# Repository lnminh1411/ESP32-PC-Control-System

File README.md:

# ESP32 PC Control System

### Why would I put myself through the suffering

I needed my PC online at all time, because sometime at school or work I need to remote
control the PC back at home. And as I measured, the idle time alone costs me ~40KWh (~7usd) per month.
So, I built this for 30usd instead of buying a boring and expensive IP KVM, while adding a tons more
features to fit my over-engineering stuffs hobby.

<table><tr><td width="190" valign="top">

</td><td valign="top">

An ESP32-S3 carrier board that lives inside a PC case. It drives three 2.4"
displays, turns the PC on and off, presses the motherboard's reset line and
works a 4-button door remote, all from one ESP32-S3-N16R8 module on a custom
2-layer PCB. A Windows helper feeds it the PC's stats and carries its
commands back to the PC.

</td></tr></table>

## Companion projects

This is the main project; the others work with it.

| Project | Role for this board |
|---|---|
| [PC Hardware Control Service](https://github.com/lnminh1411/PC-Hardware-Control-Service) (PcHwCtl) | Windows service the helper calls over the `PcHwCtl` pipe: sensor feed, fans and RGB, monitors, power actions, Process Lasso night config, webcam presence and screenshots |
| [Local LLM stack](https://github.com/lnminh1411/local-llm-stack) | Local AI stack. Its status shows on the panels, and the Discord Local Agent tab controls it through the helper's `!ai` relay |
| [ESP32 Human Presence Radar](https://github.com/lnminh1411/ESP32-Human-Presence-Radar) | Add-on presence board (mmWave radar and ToF) for the presence rules (AFK, away, intruder lock, night). New; the link to this board is in development |

*Every face, captured from the board with `shot`. The stats are made up; the
layout is real. What each panel shows and when: [docs/screens.md](docs/screens.md).*

## What it does

- **Three status panels:** PC stats, media with cover art, Claude and
  Antigravity quota and the local AI while the PC is on; a GIF, the weather
  and a clock while it is off.
- **Power control:** Wake-on-LAN and USB wake, sleep / hibernate / restart /
  shutdown / lock through PcHwCtl on the PC, and a hardware reset for a hung PC.
- **Discord bot:** a control panel for the door, the PC, its RGB, fans,
  monitors and local AI agent, and the board itself; PC, weather and log
  channels, copied to Pushover.
- **Weather:** rain nowcast and warnings (Drizzle to Typhoon) that follow
  your phone through OwnTracks, OpenWeather minute rain and GDACS typhoons.
- **Night mode:** dims everything, parks background processes on E-cores,
  sleeps the PC after an idle hour at night and hibernates it when you leave
  home.
- **Door remote:** four opto-isolated keyfob buttons.

## Parts

- **Board:** rev 3.1 carrier, 45.7 x 138.2 mm, 3 ST7789 panels on one SPI
  bus, 5 optocouplers, a 12 V boost ([docs/hardware.md](docs/hardware.md)).
- **Firmware:** ESP-IDF 5.5.6 with LovyanGFX, in [`firmware/`](firmware/)
  ([docs/firmware.md](docs/firmware.md)).
- **PC helper:** `ESP32-Helper.exe`, a .NET 10 Windows service with a
  user-session half, in [`host/pc_stats/`](host/pc_stats/)
  ([docs/helper.md](docs/helper.md)).
- **PcHwCtl:** a separate repo on the PC that owns sensors, power actions,
  RGB, fans, monitors, Process Lasso rules, the desk camera check and
  screenshots; the helper talks to it over its named pipe.
- **LocalAIHost:** a separate repo on the PC that hosts the local language
  model; the helper relays the board's local AI commands to it and polls its
  status hub.
- **Case:** a 3D-printed block, lid and display mask in
  [`enclosure/`](enclosure/).

## Quick start

1. Copy `firmware/main/settings_example.h` to `settings.h` and fill in the
   secrets ([docs/settings.md](docs/settings.md)).
2. Build and flash over USB ([docs/build-and-flash.md](docs/build-and-flash.md)):

   ```bash
   firmware/idf.cmd build
   python scripts/idf_flash.py --no-build
   ```

3. Build and install the PC helper from an elevated shell
   ([docs/helper.md](docs/helper.md#build-and-install)):

   ```bash
   host/pc_stats/build.cmd
   powershell -ExecutionPolicy Bypass -File host/pc_stats/install.ps1
   ```

4. Set the BIOS and Windows up for Wake-on-LAN
   ([docs/power-and-night.md](docs/power-and-night.md)), then set a home with
   `weather home <lat>,<lon>` on the console ([docs/console.md](docs/console.md)).

## Documentation

| Page | Covers |
|---|---|
| [screens.md](docs/screens.md) | The faces, warnings on them, PC usage warnings |
| [hardware.md](docs/hardware.md) | The board, pin map, assembly, the eFuse fix, bring-up findings, building the PCB |
| [firmware.md](docs/firmware.md) | Modules, display pipeline, tasks, ESP-IDF options, PSRAM hardening |
| [console.md](docs/console.md) | Every console command |
| [power-and-night.md](docs/power-and-night.md) | Power control, Wake-on-LAN setup, night and low power mode, the power-on brownout |
| [discord.md](docs/discord.md) | Channels, the control panel, Pushover, screenshots |
| [weather.md](docs/weather.md) | Weather sources, nowcast, warnings, OwnTracks, Pushover, call budgets |
| [helper.md](docs/helper.md) | The PC helper; full reference in [host/pc_stats/README.md](host/pc_stats/README.md) |
| [settings.md](docs/settings.md) | `settings.h`, the secrets, and [every other key](docs/settings-reference.md) |
| [build-and-flash.md](docs/build-and-flash.md) | Building, flashing, uploads, screenshots, CI |
| [layouts.md](docs/layouts.md) | JSON dashboard layouts |
| [benchmark.md](docs/benchmark.md) | Memory and speed measurements |
| [security.md](docs/security.md) | Accepted risks, where secrets live, what to check if an attack is suspected |
| [pc-power-detection.md](docs/pc-power-detection.md), [recovery-and-physical-access.md](docs/recovery-and-physical-access.md) | Design notes |
| [documentations_summary.md](docs/documentations_summary.md) | Every doc in the repo in one list |

## Repository layout

| Path | Contents |
|---|---|
| [`firmware/`](firmware/) | The board's firmware |
| [`host/pc_stats/`](host/pc_stats/) | The PC helper ([README](host/pc_stats/README.md)) |
| [`pcb/`](pcb/) | atopile netlist, KiCad board, footprints ([README](pcb/README.md)) |
| [`scripts/`](scripts/) | PCB build chain, flashing, uploads, screenshots ([README](scripts/README.md)) |
| [`enclosure/`](enclosure/) | CadQuery model of the case ([README](enclosure/README.md)) |
| [`docs/`](docs/) | The pages above |

## Status

Rev 3.1 is fabricated and assembled, and the firmware runs on it: all three
panels, PC power detection, the stats link, Wi-Fi, Wake PC, the Discord bot,
live weather with OwnTracks and Pushover, and night mode are in daily use.
Still to do: test the door buttons B1-B4 on the real keyfob, and
build the firmware in CI.

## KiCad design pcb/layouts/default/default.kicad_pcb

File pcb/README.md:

# Carrier PCB (atopile + KiCad), rev 3.1

Single-file atopile project: [`main.ato`](main.ato), the source of truth
for the netlist. It has no external imports: every part is defined locally
with explicit pins and footprint. The KiCad board is
`layouts/default/default.kicad_pcb`, generated and routed by the scripts in
[`../scripts/`](../scripts/README.md).

## Build

```bash
cd pcb
PYTHONIOENCODING=utf-8 ato build
```

`PYTHONIOENCODING=utf-8` works around a Windows-console crash in atopile's
`designator-map` step (a `rich`/`colorama` Unicode bug). `ato build` only
writes the netlist; [`../scripts/sync_netlist_to_board.py`](../scripts/sync_netlist_to_board.py)
puts it onto the board. The full chain is in
[`../scripts/README.md`](../scripts/README.md).

If you regenerate `ato.yaml`, the version key is **`ato-version`**
(hyphenated). The underscore form fails with an unrelated-looking
"not valid SemVer string" error.

## Board

- **L-shaped, 45.7 x 138.2 mm**, 1.6 mm thick, **2 layers**, DRC 0/0.
  Main body 45.7 x 88.0 mm, plus a 16.7 mm strip down the east edge that
  carries displays 2 and 3.
- The ESP32 module is mounted **rotated 180°**: the USB-C end overhangs the
  **top** edge (the enclosure's plug-in side), the PCB antenna is at the
  bottom of the module with a no-copper keepout under it (all layers,
  Y = 54.5-67.5 mm). The main body continues below the antenna to hold the
  RST pair, keyfob socket and status LED, so expect slightly less WiFi/BLE
  range than with the antenna over air.
- The boost, the 5 optos and 11 of the axial resistors sit **under the
  module**, which rides ~11 mm up on its sockets (boost top ~6.5 mm, ~4.5 mm
  clearance).
- **Displays plug in directly**: GMT024-08-SPI8P 2.4" panels (PCB 46.9 x
  71 mm, 8-pin header) in right-angle sockets at **51.9 mm pitch**,
  overhanging the east edge 1 mm so the panel header clears. Pin order
  GND VCC SCL SDA RST DC CS BL = socket pads 1-8. **Panels hang down below
  the board**, screen facing out, header edge up: the only way round that
  puts panel pin 1 (GND) on pad 1. Plugged in standing up, all 8 pins
  reverse (5V onto CS).
- Mounting holes (M2.5): top-right, bottom-left of the main body, between
  displays 1/2 and between displays 2/3.

### Stackup and routing

- **F.Cu carries all routing; B.Cu is one unbroken GND pour** except 5
  short B.Cu jumpers (27 mm total, 6 vias) where a line must cross the
  display bus or the opto anode bus. No B.Cu jumper crosses under SCK or
  MOSI. Every part is through-hole, so the pour connects every GND pad.
- **5V is a routed 0.4-0.5 mm track** (net class `Power`: 0.5 mm track,
  0.8/0.4 mm via, covers 5V and 12V) from J1 pin 21 down the west side of
  J1 to a trunk under the display sockets. 12V (boost -> opto collectors,
  keyfob) is a 0.5 mm bus, 0.4 mm to the keyfob. Nothing uses 3V3.
- **Display bus**: SCK, MOSI and DC are a true daisy chain on F.Cu (MCU ->
  display 1 -> 2 -> 3, every segment pad to pad, no T-junctions, no vias).
  SCK and MOSI each pass a **33R THT series resistor** (source termination;
  fit a wire link to bypass) lying flat in the top-right corner. CS1-3 and
  RST1-3 are point-to-point. Chain lengths: SCK 144 mm, MOSI 146 mm, DC
  147 mm. Verified by [`../scripts/check_spi_topology.py`](../scripts/check_spi_topology.py).
- **Everything is hand-routed** by [`../scripts/route_spi.py`](../scripts/route_spi.py);
  Freerouting stays only as a safety net. Every track corner is a 45°
  chamfer.
- **SI note**: on 2 layers the SPI return path is the B.Cu pour 1.6 mm
  below, and three jumper slots (BL2, BL3, RST2, each <= 6 mm) cross under
  the bus lanes in the strip. The bus runs at 40 MHz (see the root README);
  if a panel ever shows noise, lower the SPI clock first.

**Net names** are declared explicitly in `main.ato` (`gnd`, `v5`, `v12`,
`disp_*`, `mb_rst`, `mb_rst_gnd`, `led_a`). Without them atopile names each
net after a random member pin.

**Board references come from the atopile instance names** (J1 `mcu.left`,
J2 `mcu.right`, J3-J5 displays, J6 RST pair, J7 keyfob, PS1 boost, U1-U5
`opto1-5`, R1-R13, D1 LED), not atopile's declaration-order numbers, so
adding or removing a part does not renumber the rest.

### Silkscreen

- Every off-board connector has per-pin labels (displays
  GND/5V/SCL/SDA/RSTn/DC/CSn/BLn, keyfob 12V/B1-B4/GND, RST pair).
- **Module**: "USB-C END (TOP EDGE)" at the top edge, "ANTENNA END" at the
  bottom; pin 1 of each row labelled (left row J2 = GND, right row J1 = 3V3).
- **Resistors**: the value is printed inside each body (`270R` x6, `10k`
  x5, `33R` x2).
- **PC817 optos**: pin 1 (LED anode) is the square pad and has a **dot**,
  matching the part's moulded dot. Place dot to dot.

## Parts

| Connector / part | Pins | Footprint / notes |
|---|---|---|
| N16R8 module socket (J1, J2) | 44 (2x22) | Female; the module plugs in on its own male headers. Socket row spacing is 25.4 mm, measured off the real module (not Espressif's 22.86 mm reference). |
| Boost converter (PS1) | 4 | CKCS BS01 5V->12V, custom footprint `footprints/ESP32PCC.pretty/Boost_CKCS_BS01` (pads measured ±0.15 mm). Mount on 4 single male pins: long end down through the board, short end up through the module. Set the A+B bridges for 12V and meter it before connecting the keyfob. |
| Keyfob connector (J7) | 1x6 | Female right-angle, bottom edge of the main body: 1 = 12V, 2-5 = B1-B4 (opto 1-4 emitters), 6 = GND |
| Display sockets (J3-J5) | 3x 1x8 | Female right-angle, see Board above |
| PC817 bank (U1-U5) | 5x DIP-4 | `Package_DIP:DIP-4_W7.62mm`, turned 180°, outputs facing the west edge |
| Status LED (D1) | 5 mm THT | Pad 1 (square) = cathode; below the module beside J6, for a light pipe |
| Resistors (R1-R13) | 6x 270R + 5x 10k + 2x 33R | Axial DIN0207 lying flat, leads bent to the measured 8.128 mm pitch: 5 opto LED drive, 1 status LED, 5 opto-GPIO pull-downs, 2 SCK/MOSI series terminations |
| Motherboard RST pair (J6) | 1x2 | Female right-angle, west edge below the module: 1 = opto 5 collector (to RST+), 2 = emitter (to RST GND) |

The PC link (USB-OTG, the module's second USB-C port) is a Type-E-to-Type-C
cable straight to the motherboard's internal USB header. No carrier copper.

## Pin mapping

The table is in the [root README](../README.md#pin-map-rev-31). Design
reasons behind it:

- Display bus on FSPI IO_MUX pins (MOSI 11, SCK 12). Per-display RST lines
  so a hung panel can be reset alone. BL1 is GPIO3 (pin 13, below the bus):
  pin 19 sits inside the loop the SCK/MOSI risers make, and a jumper there
  would cut the GND pour under both fast lines. GPIO3 is a strap pin only
  when the JTAG-select eFuse is burnt (it isn't by default).
- Opto drive GPIOs (B1-B4 = 39/40/41/42, reset = 1) follow J2's pin order so
  the drive lines reach the optos without crossing. GPIO1 for the reset
  line has no boot-time pull-up glitch.
- **Every opto GPIO has a 10k pull-down.** GPIO39-42 are JTAG pins that can
  come up with a ~45k pull-up during reset/boot/flashing, and ~50 µA through
  an opto is enough for the fob's CMOS button input to see a phantom press.
  With 10k the pin sits at ~0.6 V, below the LED's ~1.1 V turn-on.
- Display VCC is the module's 5Vin, not 3V3, on purpose: the panels have
  their own 3.3V regulator. **Bridge the module's `IN-OUT` jumper**: by
  default `5VIN` is input-only and the carrier gets no 5V.
- Unused module GPIOs: 0, 4, 7, 13, 14, 21, 38, 45, 46, 47, 48 (48 = onboard
  WS2812).

### Opto GPIO rules (firmware)

All five opto pins are initialised the same way, implemented in
[`../firmware/main/optos.cpp`](../firmware/main/optos.cpp):
pre-stage the output latch LOW with `gpio_set_level(pin, 0)` while the pin
is still Hi-Z, then switch it to an output with `gpio_config`. The pin goes
Hi-Z (held low by the 10k) -> driven LOW, with no window where it can drive
HIGH. `optosInit()` is the first thing `app_main` runs. Pulses are ended by
one-shot `esp_timer`s.

- Reset is a short pulse only (HIGH 200 ms, then LOW). Holding it HIGH keeps
  the PC in reset; it never powers it off.
- Never pulse reset at boot: the ESP is powered from the PC's USB, so a
  reset at boot could loop forever.
- Never use `INPUT_PULLUP` on an opto GPIO: the ~45k internal pull-up
  against the 10k pull-down lands near the opto LED's turn-on voltage.
- The board has no hardware interlock between door buttons; the
  one-at-a-time rule and the 500 ms gap live in firmware.

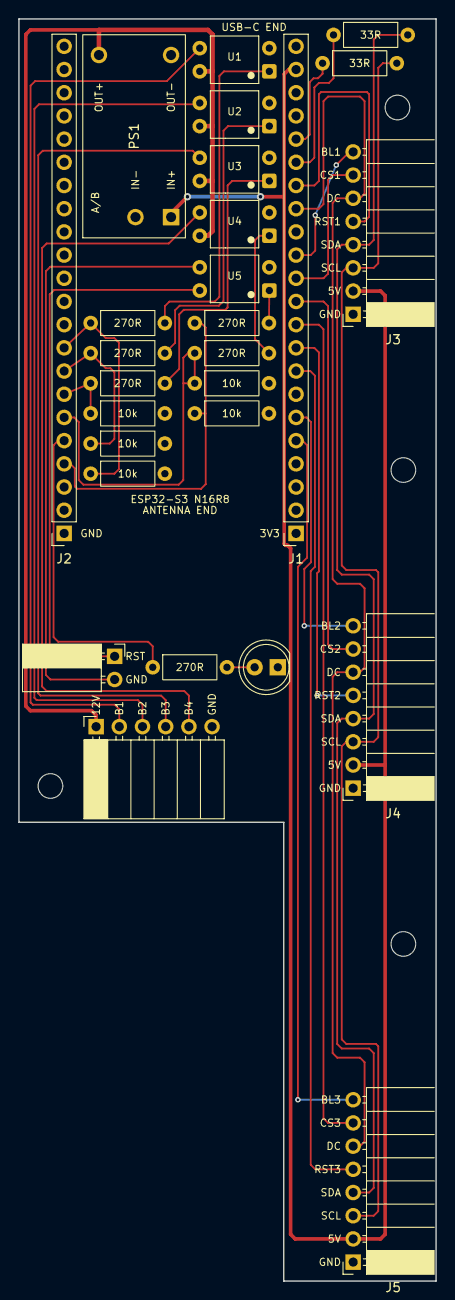
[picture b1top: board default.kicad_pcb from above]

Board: 2 copper layers, 45.7 x 138.2 mm, 31 parts (0 on the bottom side), 35 nets.

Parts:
D1: main.ato:StatusLED; LED_D5.0mm
J1, J2: main.ato:Header1x22; PinSocket_1x22_P2.54mm_Vertical
J3, J4, J5: main.ato:DisplaySocket; PinSocket_1x08_P2.54mm_Horizontal
J6: main.ato:IsolatedPair; PinSocket_1x02_P2.54mm_Horizontal
J7: main.ato:KeyfobSocket; PinSocket_1x06_P2.54mm_Horizontal
MH1, MH2, MH3, MH4: MountingHole_2.7mm_M2.5
PS1: main.ato:BoostModuleBS01; Boost_CKCS_BS01
R1, R2, R3, R4, R5, R6: 270R; R_Axial_DIN0207_L6.3mm_D2.5mm_P10.16mm_Horizontal
R7, R10, R11, R12, R13: 10k; R_Axial_DIN0207_L6.3mm_D2.5mm_P10.16mm_Horizontal
R8, R9: 33R; R_Axial_DIN0207_L6.3mm_D2.5mm_P10.16mm_Horizontal
U1, U2, U3, U4, U5: main.ato:Optocoupler; DIP-4_W7.62mm

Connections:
btn1: J7.2, U1.3
btn2: J7.3, U2.3
btn3: J7.4, U3.3
btn4: J7.5, U4.3
disp_bl1: J1.13, J3.8
disp_bl2: J1.6, J4.8
disp_bl3: J1.5, J5.8
disp_dc: J1.15, J3.6, J4.6, J5.6
disp_mosi: J3.4, J4.4, J5.4, R9.2
disp_rst1: J1.16, J3.5
disp_rst2: J1.9, J4.5
disp_rst3: J1.8, J5.5
disp_sck: J3.3, J4.3, J5.3, R8.2
gnd: D1.1, J1.22, J2.1, J2.21, J2.22, J3.1, J4.1, J5.1, J7.6, PS1.2, PS1.4, R7.2, R10.2, R11.2, R12.2, R13.2, U1.2, U2.2, U3.2, U4.2, U5.2
gpio1: J2.4, R5.1, R10.1
gpio2: J2.5, R6.1
gpio8: J1.12, J3.7
gpio11: J1.17, R9.1
gpio12: J1.18, R8.1
gpio17: J1.10, J5.7
gpio18: J1.11, J4.7
gpio39: J2.9, R1.1, R7.1
gpio40: J2.8, R2.1, R13.1
gpio41: J2.7, R3.1, R12.1
gpio42: J2.6, R4.1, R11.1
led_a: D1.2, R6.2
mb_rst: J6.1, U5.4
mb_rst_gnd: J6.2, U5.3
opto1-anode: R1.2, U1.1
opto2-anode: R2.2, U2.1
opto3-anode: R3.2, U3.1
opto4-anode: R4.2, U4.1
opto5-anode: R5.2, U5.1
v5: J1.21, J3.2, J4.2, J5.2, PS1.1
v12: J7.1, PS1.3, U1.4, U2.4, U3.4, U4.4

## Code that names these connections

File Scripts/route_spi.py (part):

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ROUTES["disp_rst1"] = [(XR, u1(16)), (lane(3), u1(16)), (lane(3), 8.0),
                       (XD + 1.75, 8.0), (XD + 1.75, dpad(0, 5)), (XD, dpad(0, 5))]

# module pin -> series resistor pad 1 (separate nets: gpio12 / gpio11):
# east to the riser lane, north, jog east, north into pad 1. MOSI's riser
# rises past R8 pad 1 on its east side to reach the top row.
ROUTES[("R8", "1")] = [(XR, u1(18)), (lane(1), u1(18)), (lane(1), SCK_JOG_Y),
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    # 0.42 pitch (0.22 gaps: chamfer_corners needs > 0.21 to cut the bends);
    # 12V narrows to 0.4 here (keyfob supply only), 0.55 from the board edge
    LANE = {"v12": XL - 4.2, "btn1": XL - 3.68, "btn2": XL - 3.26, "btn3": XL - 2.84,
            "btn4": XL - 2.42, "mb_rst_gnd": XL - 2.0, "mb_rst": XL - 1.58, "gpio2": XL - 1.16}
    # 12V: the bus's top run continues west over J2's top end (a 0.5mm track
    # doesn't fit between J2 pads) into the westmost lane
    EXTRA.append(("v12", pcbnew.F_Cu, PW, [(OUT_POS[0], V12_TOP), (LANE["v12"], V12_TOP)]))
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        px = J7P[0] + 2.54 * i
        END[net] = [(LANE[net], J7_ROW[net]), (px, J7_ROW[net]), (px, J7P[1])]
    for net, (ox, oy), gy in OUTS:
        if net == "btn4":   # SW past U4's pin 4 + boost IN+, then west at the gap
            head = [(ox, oy), (ox - 1.45, oy + 1.45), (ox - 1.45 - (gy - oy - 1.45), gy)]
        else:
            head = [(ox, oy), (ox - abs(gy - oy), gy)]
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    EXTRA.append(("v12", pcbnew.F_Cu, PW, [(LANE["v12"], V12_TOP)] + END["v12"]))
    # LED: J2 pin 5 -> east-most lane -> above J6 pin 1 -> R6 -> D1 anode
    LED_Y = 68.2                         # between the keepout (67.5) and J6 pin 1
    EXTRA.append(("gpio2", pcbnew.F_Cu, TRACK_W, [(XL, j2(5)), (LANE["gpio2"], j2(5)),
                                                  (LANE["gpio2"], LED_Y), (R6P[0], LED_Y), R6P]))
    EXTRA.append(("led_a", pcbnew.F_Cu, TRACK_W, [(R6P[0] + 8.128, R6P[1]), D1A]))

    # rev 3 opto drive: J2 -> 270R (+ 10k pull-down) -> opto LED anode, all
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    ROW = dict(a=33.3, b=36.6, c=39.9, d=43.2, e=46.5, f=49.8)
    OPTO_E = OPTO_W + 7.62               # opto LED pins (pin 1 anode)
    an = {k: 5.74 + 6 * (k - 1) for k in range(1, 6)}  # U1-U5 anode Y
    # GPIO39/40/41 -> R1/R2/R3 (west a,b,c) straight from J2 pins 9/8/7; the
    # pull-downs hang below: GPIO41 -> R12 (west d) straight down the pad
    # column, GPIO40/39 -> R13/R7 (west e,f) down under the west bodies
    EXTRA.append(("gpio39", pcbnew.F_Cu, TRACK_W, [(XL, j2(9)), (W1, ROW["a"])]))
    EXTRA.append(("gpio40", pcbnew.F_Cu, TRACK_W, [(XL, j2(8)), (W1, ROW["b"])]))
    EXTRA.append(("gpio41", pcbnew.F_Cu, TRACK_W, [(XL, j2(7)), (W1, ROW["c"])]))
    EXTRA.append(("gpio41", pcbnew.F_Cu, TRACK_W, [(W1, ROW["c"]), (W1, ROW["d"])]))
    for net, r, gap, cx, pd in (("gpio40", "b", 38.25, W1 + 2.6, "e"),
                                ("gpio39", "a", 34.95, W1 + 3.1, "f")):
        EXTRA.append((net, pcbnew.F_Cu, TRACK_W, [(W1, ROW[r]), (W1 + gap - ROW[r], gap), (cx, gap),
                                                  (cx, ROW[pd]), (W1, ROW[pd])]))
    # GPIO42 / GPIO1 (J2 pins 6/4): down beside J2, east under the bank, up
    # either side of the east pad-1 column -> R4 + pull-down R11 (west side),
    # R5 + pull-down R10 (east side)
    G42_X, G1_X = E1 - 1.25, E1 + 1.2
    EXTRA.append(("gpio42", pcbnew.F_Cu, TRACK_W, [(XL, j2(6)), (XL + 1.6, j2(6)), (XL + 1.6, 51.0),
                                                   (G42_X, 51.0), (G42_X, ROW["b"]), (E1, ROW["b"])]))
    EXTRA.append(("gpio42", pcbnew.F_Cu, TRACK_W, [(G42_X, ROW["c"]), (E1, ROW["c"])]))
    EXTRA.append(("gpio1", pcbnew.F_Cu, TRACK_W, [(XL, j2(4)), (XL + 1.17, j2(4)), (XL + 1.17, 51.45),
                                                  (G1_X, 51.45), (G1_X, ROW["a"]), (E1, ROW["a"])]))
    EXTRA.append(("gpio1", pcbnew.F_Cu, TRACK_W, [(G1_X, ROW["d"]), (E1, ROW["d"])]))
    # anodes: west column (R1-R3 -> U1-U3) north between the columns, east
    # along the gap under U5, up the DIP corridor (lanes west->east U1-U3) and
    # peel east onto each anode pin; R4 -> U4 up a lane east of the corridor,
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
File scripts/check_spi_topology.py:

"""
Verifies the display-bus routing that route_spi.py lays down: every display
net (SCK, MOSI, DC, RST1 + CS1-3; RST2/3 are routed separately) is F.Cu only, has no vias, has NO node
where 3+ track ends meet (a T-junction / star), and walks as a single chain
from the MCU pad through each display pad in order.

    <kicad-python> scripts/check_spi_topology.py

Run after route_board.py (or any manual edit in KiCad touching these nets).
Coordinates are compared at 1um resolution: pad centres on the 180-degree
display sockets land ~1nm off round mm values.
"""
import pcbnew
from board_config import BOARD_PATH
from collections import Counter
mm=pcbnew.ToMM
b=pcbnew.LoadBoard(BOARD_PATH)
fps={f.GetReference():f for f in b.GetFootprints()}
nets=["gpio12","disp_sck","gpio11","disp_mosi","disp_dc","disp_rst1"]+[fps[r].FindPadByNumber("7").GetNetname() for r in ("J3","J4","J5")]
for n in nets:
    tr=[t for t in b.GetTracks() if t.GetNetname()==n]
    deg=Counter()
    for t in tr:
        deg[(round(t.GetStart().x,-3),round(t.GetStart().y,-3))]+=1; deg[(round(t.GetEnd().x,-3),round(t.GetEnd().y,-3))]+=1
    pads={(round(p.GetPosition().x,-3),round(p.GetPosition().y,-3)):f"{p.GetParentFootprint().GetReference()}.{p.GetNumber()}" for p in b.GetPads() if p.GetNetname()==n}
    tees=[(round(mm(x),2),round(mm(y),2),d) for (x,y),d in deg.items() if d>=3]
    order=[]  # walk chain from the MCU pad
    start=[k for k,v in pads.items() if v.split(".")[0] not in ("J3","J4","J5")][0]  # MCU pad or its series resistor
    adj={}
    for t in tr:
        a=(round(t.GetStart().x,-3),round(t.GetStart().y,-3)); c=(round(t.GetEnd().x,-3),round(t.GetEnd().y,-3))
        adj.setdefault(a,[]).append(c); adj.setdefault(c,[]).append(a)
    seen={start}; cur=start; length=0
    while True:
        if cur in pads: order.append(pads[cur])
        nxt=[p for p in adj.get(cur,[]) if p not in seen]
        if not nxt: break
        length+=((nxt[0][0]-cur[0])**2+(nxt[0][1]-cur[1])**2)**0.5; seen.add(nxt[0]); cur=nxt[0]
    layers={b.GetLayerName(t.GetLayer()) for t in tr}
    vias=sum(1 for t in tr if t.GetClass()=="PCB_VIA")
    print(f"{n:10s} layers={layers} vias={vias} T/star nodes={tees or 'none'} chain={' -> '.join(order)} len={mm(length):.1f}mm")
